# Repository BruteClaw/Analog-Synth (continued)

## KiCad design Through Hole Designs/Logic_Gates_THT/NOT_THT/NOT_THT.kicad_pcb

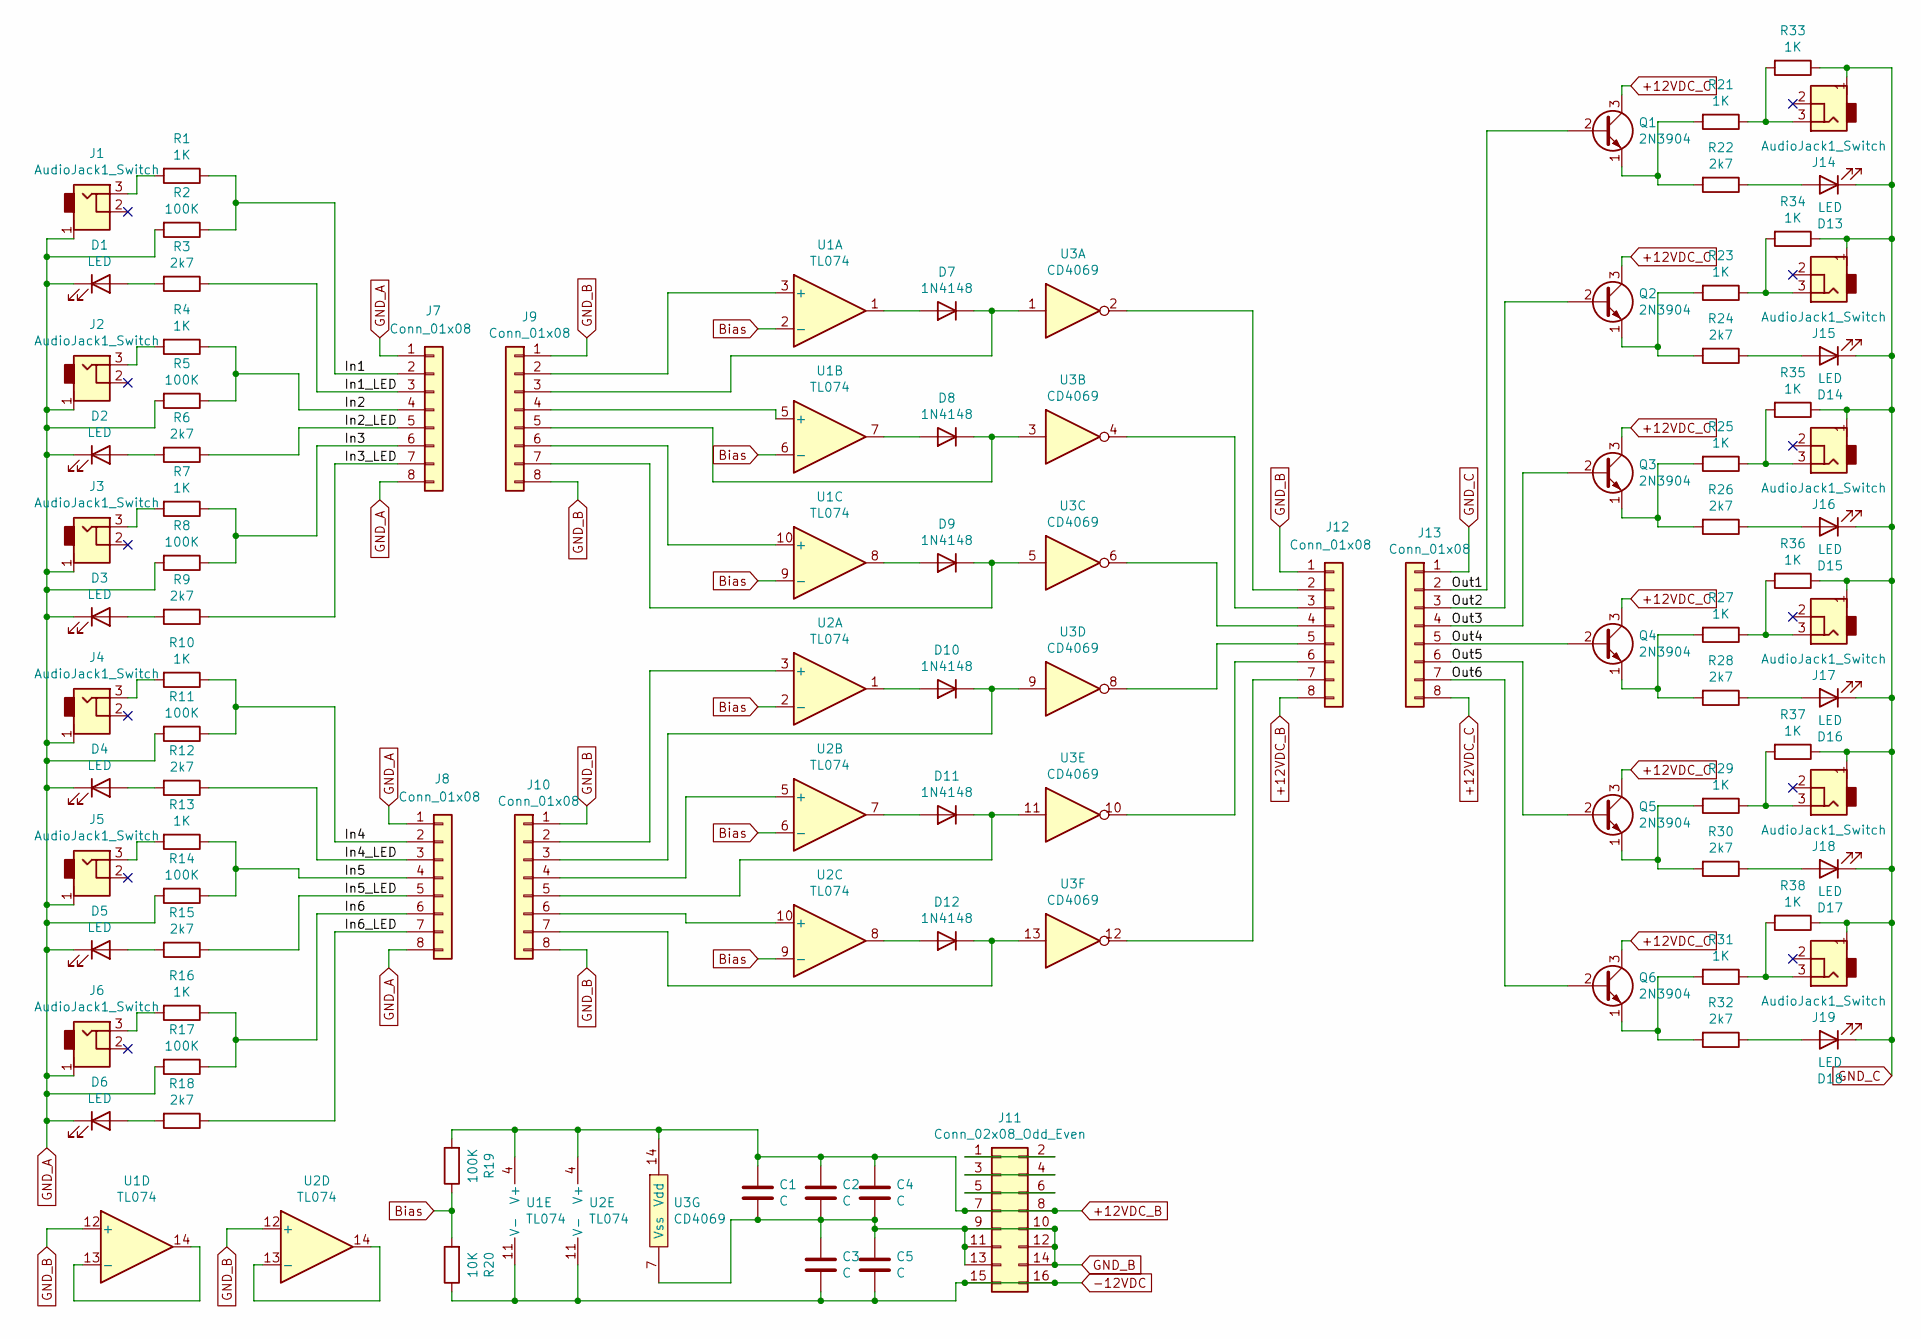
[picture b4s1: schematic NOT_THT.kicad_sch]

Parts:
C1, C2, C3, C4, C5: C; C_Disc_D5.0mm_W2.5mm_P2.50mm
D1, D2, D3, D4, D5, D6, D13, D14, D15, D16, D17, D18: LED; LED_Rectangular_W3.9mm_H1.9mm
D7, D8, D9, D10, D11, D12: 1N4148; D_DO-35_SOD27_P7.62mm_Horizontal
J1, J2, J3, J4, J5, J6, J14, J15, J16, J17, J18, J19: AudioJack1_Switch; Mono_Jack_3.5mm_Switch_Switchcraft_35RAPC2AH3
J7, J8, J9, J10, J12, J13: Conn_01x08; Pin_Header_Straight_1x08_Pitch2.54mm
J11: Conn_02x08_Odd_Even; Pin_Header_Straight_2x08_Pitch2.54mm
Q1, Q2, Q3, Q4, Q5, Q6: 2N3904; TO-92_Inline_Wide
R1, R4, R7, R10, R13, R16, R21, R23, R25, R27, R29, R31, R33, R34, R35, R36, R37, R38: 1K; R_Axial_DIN0207_L6.3mm_D2.5mm_P10.16mm_Horizontal
R2, R5, R8, R11, R14, R17, R19: 100K; R_Axial_DIN0207_L6.3mm_D2.5mm_P10.16mm_Horizontal
R3, R6, R9, R12, R15, R18, R22, R24, R26, R28, R30, R32: 2k7; R_Axial_DIN0207_L6.3mm_D2.5mm_P10.16mm_Horizontal
R20: 10K; R_Axial_DIN0207_L6.3mm_D2.5mm_P10.16mm_Horizontal
U1, U2: TL074; DIP-14_W7.62mm_Socket
U3: CD4069; DIP-14_W7.62mm_Socket

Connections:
+12VDC_B: C1.1, C2.1, C4.1, J11.7, J11.8, J12.8, R19.2, U1.4 (V+), U2.4 (V+), U3.14 (Vdd)
+12VDC_C: J13.8, Q1.3 (C), Q2.3 (C), Q3.3 (C), Q4.3 (C), Q5.3 (C), Q6.3 (C)
-12VDC: C3.2, C5.2, J11.15, J11.16, R20.1, U1.11 (V-), U2.11 (V-)
/In1: J7.2, R1.1, R2.1
/In1_LED: J7.3, R3.1
/In2: J7.4, R4.1, R5.1
/In2_LED: J7.5, R6.1
/In3: J7.6, R7.1, R8.1
/In3_LED: J7.7, R9.1
/In4: J8.2, R10.1, R11.1
/In4_LED: J8.3, R12.1
/In5: J8.4, R13.1, R14.1
/In5_LED: J8.5, R15.1
/In6: J8.6, R16.1, R17.1
/In6_LED: J8.7, R18.1
/Out1: J13.2, Q1.2 (B)
/Out2: J13.3, Q2.2 (B)
/Out3: J13.4, Q3.2 (B)
/Out4: J13.5, Q4.2 (B)
/Out5: J13.6, Q5.2 (B)
/Out6: J13.7, Q6.2 (B)
Bias: R19.1, R20.2, U1.2 (-), U1.6 (-), U1.9 (-), U2.2 (-), U2.6 (-), U2.9 (-)
GND_A: D1.1 (K), D2.1 (K), D3.1 (K), D4.1 (K), D5.1 (K), D6.1 (K), J1.1, J2.1, J3.1, J4.1, J5.1, J6.1, J7.1, J7.8, J8.1, J8.8, R2.2, R5.2, R8.2, R11.2, R14.2, R17.2
GND_B: C1.2, C2.2, C3.1, C4.2, C5.1, J9.1, J9.8, J10.1, J10.8, J11.9, J11.10, J11.11, J11.12, J11.13, J11.14, J12.1, U1.12 (+), U2.12 (+), U3.7 (Vss)
GND_C: D13.1 (K), D14.1 (K), D15.1 (K), D16.1 (K), D17.1 (K), D18.1 (K), J13.1, J14.1, J15.1, J16.1, J17.1, J18.1, J19.1, R33.1, R34.1, R35.1, R36.1, R37.1, R38.1
unnamed: D1.2 (A), R3.2
unnamed: D2.2 (A), R6.2
unnamed: D3.2 (A), R9.2
unnamed: D4.2 (A), R12.2
unnamed: D5.2 (A), R15.2
unnamed: D6.2 (A), R18.2
unnamed: D7.1 (K), J9.3, U3.1
unnamed: D7.2 (A), U1.1
unnamed: D8.1 (K), J9.5, U3.3
unnamed: D8.2 (A), U1.7
unnamed: D9.1 (K), J9.7, U3.5
unnamed: D9.2 (A), U1.8
unnamed: D10.1 (K), J10.3, U3.9
unnamed: D10.2 (A), U2.1
unnamed: D11.1 (K), J10.5, U3.11
unnamed: D11.2 (A), U2.7
unnamed: D12.1 (K), J10.7, U3.13
unnamed: D12.2 (A), U2.8
unnamed: D13.2 (A), R22.1
unnamed: D14.2 (A), R24.1
unnamed: D15.2 (A), R26.1
unnamed: D16.2 (A), R28.1
unnamed: D17.2 (A), R30.1
unnamed: D18.2 (A), R32.1
unnamed: J1.3, R1.2
unnamed: J2.3, R4.2
unnamed: J3.3, R7.2
unnamed: J4.3, R10.2
unnamed: J5.3, R13.2
unnamed: J6.3, R16.2
unnamed: J9.2, U1.3 (+)
unnamed: J9.4, U1.5 (+)
unnamed: J9.6, U1.10 (+)
unnamed: J10.2, U2.3 (+)
unnamed: J10.4, U2.5 (+)
unnamed: J10.6, U2.10 (+)
unnamed: J11.1, J11.2
unnamed: J11.3, J11.4
unnamed: J11.5, J11.6
unnamed: J12.2, U3.2
unnamed: J12.3, U3.4
unnamed: J12.4, U3.6
unnamed: J12.5, U3.8
unnamed: J12.6, U3.10
unnamed: J12.7, U3.12
unnamed: J14.3, R21.1, R33.2
unnamed: J15.3, R23.1, R34.2
unnamed: J16.3, R25.1, R35.2
unnamed: J17.3, R27.1, R36.2
unnamed: J18.3, R29.1, R37.2
unnamed: J19.3, R31.1, R38.2
unnamed: Q1.1 (E), R21.2, R22.2
unnamed: Q2.1 (E), R23.2, R24.2
unnamed: Q3.1 (E), R25.2, R26.2
unnamed: Q4.1 (E), R27.2, R28.2
unnamed: Q5.1 (E), R29.2, R30.2
unnamed: Q6.1 (E), R31.2, R32.2
unnamed: U1.13 (-), U1.14
unnamed: U2.13 (-), U2.14

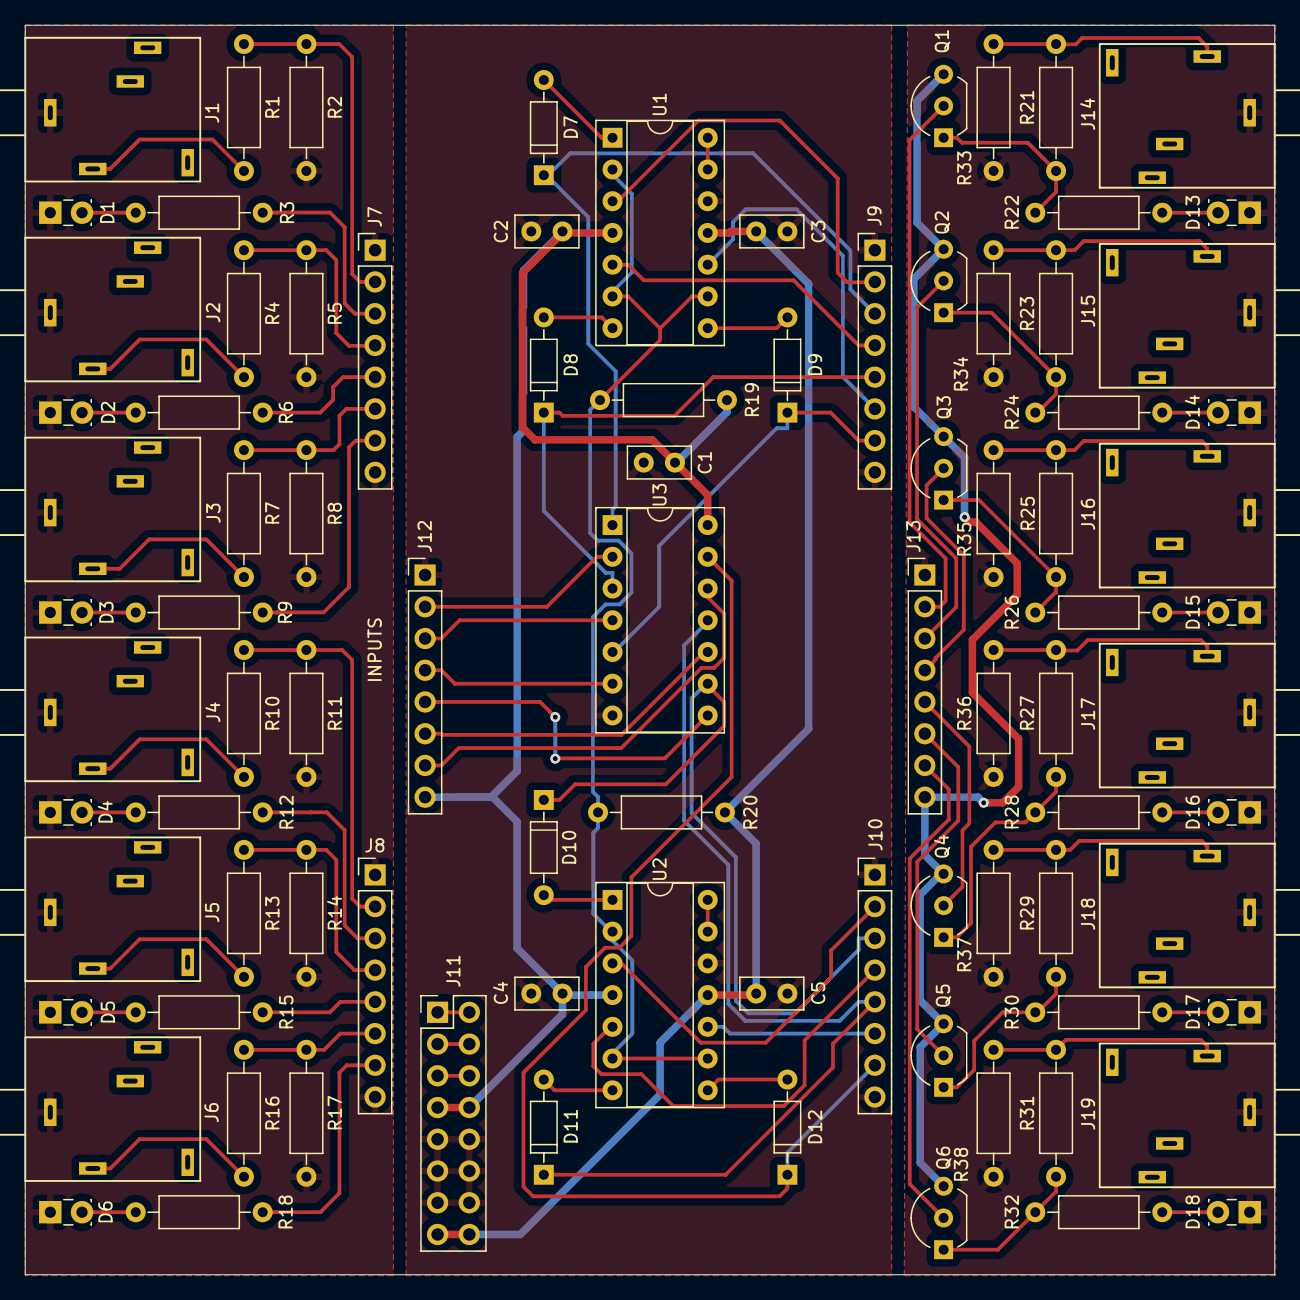
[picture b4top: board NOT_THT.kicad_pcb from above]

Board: 2 copper layers, 100.0 x 100.0 mm, 89 parts (0 on the bottom side), 84 nets.

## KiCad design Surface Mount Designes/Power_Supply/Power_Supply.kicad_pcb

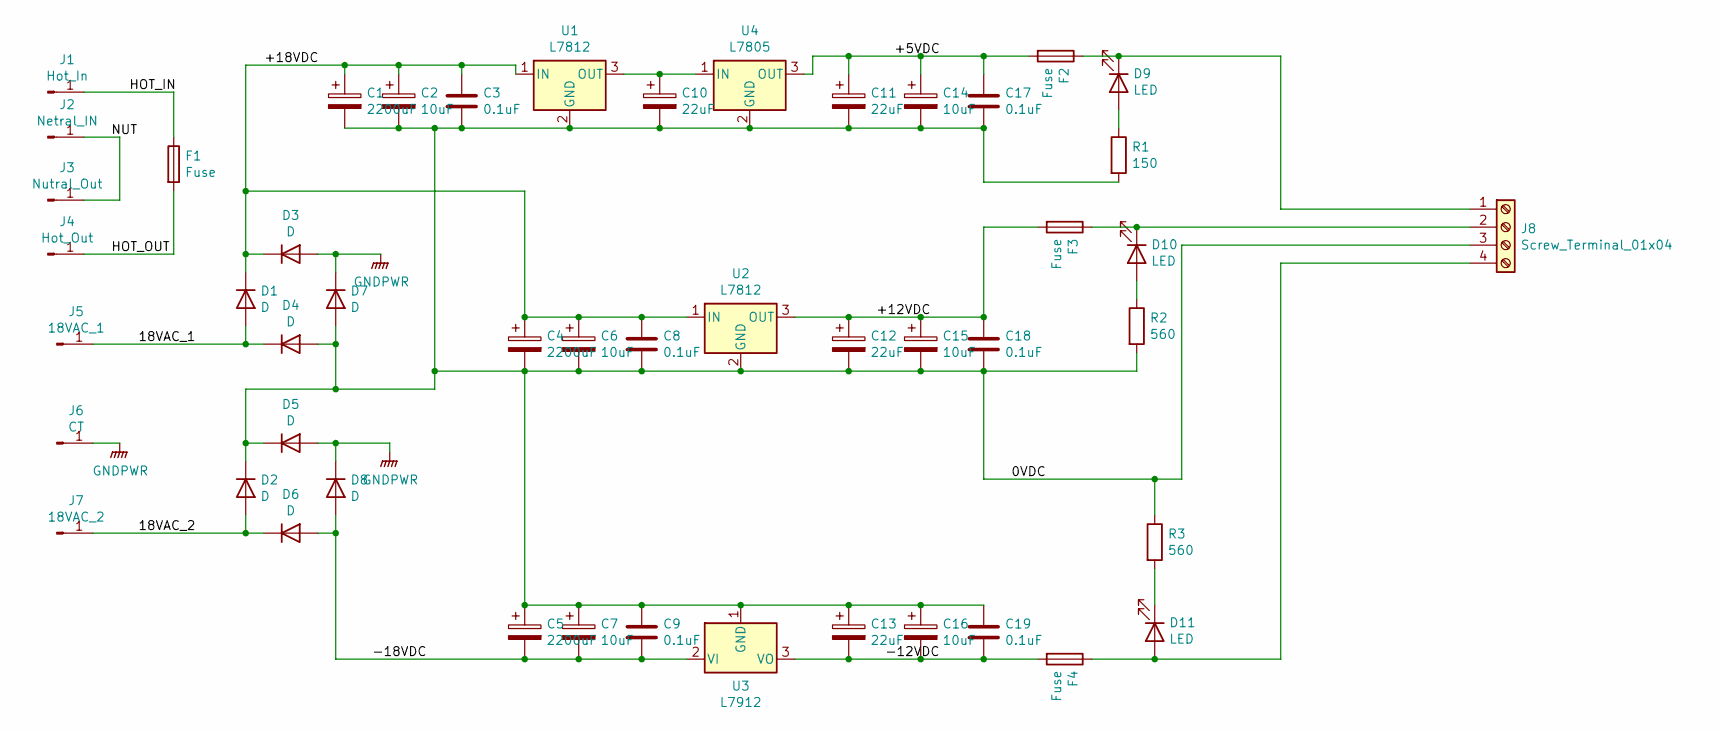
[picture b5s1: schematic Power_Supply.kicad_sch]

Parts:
C1, C4, C5: 2200uF; CP_Elec_18 x 21.5
C2, C6, C7, C14, C15, C16: 10uF; CP_Elec_5x5.3
C3, C8, C9, C17, C18, C19: 0.1uF; C_1206_HandSoldering
C10, C11, C12, C13: 22uF; CP_Elec_6.3x5.7
D1, D2, D3, D4, D5, D6, D7, D8: D; D_SMB
D9, D10, D11: LED; LED_1206_HandSoldering
F1, F2, F3, F4: Fuse; Fuseholder5x20_horiz_open_inline_Type-I
J1: Hot_In; TAB_Conn
J2: Netral_IN; TAB_Conn
J3: Nutral_Out; TAB_Conn
J4: Hot_Out; TAB_Conn
J5: 18VAC_1; TAB_Conn
J6: CT; TAB_Conn
J7: 18VAC_2; TAB_Conn
J8: Screw_Terminal_01x04; TerminalBlock_bornier-4_P5.08mm
R1: 150; R_1210_HandSoldering
R2, R3: 560; R_1210_HandSoldering
U1, U2: L7812; TO-252-2
U3: L7912; TO-263-2
U4: L7805; TO-252-2

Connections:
/0VDC: C1.2, C2.2, C3.2, C4.2, C5.1, C6.2, C7.1, C8.2, C9.1, C10.2, C11.2, C12.2, C13.1, C14.2, C15.2, C16.1, C17.2, C18.2, C19.1, D2.1 (K), D4.2 (A), D5.1 (K), D7.2 (A), J8.3, R1.2, R2.2, R3.1, U1.2 (GND), U2.2 (GND), U3.1 (GND), U4.2 (GND)
/18VAC_1: D1.2 (A), D4.1 (K), J5.1
/18VAC_2: D2.2 (A), D6.1 (K), J7.1
/+5VDC: C11.1, C14.1, C17.1, F2.2, U4.3 (OUT)
/+12VDC: C12.1, C15.1, C18.1, F3.2, U2.3 (OUT)
/+18VDC: C1.1, C2.1, C3.1, C4.1, C6.1, C8.1, D1.1 (K), D3.1 (K), U1.1 (IN), U2.1 (IN)
/-12VDC: C13.2, C16.2, C19.2, F4.2, U3.3 (VO)
/-18VDC: C5.2, C7.2, C9.2, D6.2 (A), D8.2 (A), U3.2 (VI)
/HOT_IN: F1.1, J1.1
/HOT_OUT: F1.2, J4.1
/NUT: J2.1, J3.1
GNDPWR: D3.2 (A), D5.2 (A), D7.1 (K), D8.1 (K), J6.1
unnamed: C10.1, U1.3 (OUT), U4.1 (IN)
unnamed: D9.1 (K), F2.1, J8.1
unnamed: D9.2 (A), R1.1
unnamed: D10.1 (K), F3.1, J8.2
unnamed: D10.2 (A), R2.1
unnamed: D11.1 (K), R3.2
unnamed: D11.2 (A), F4.1, J8.4

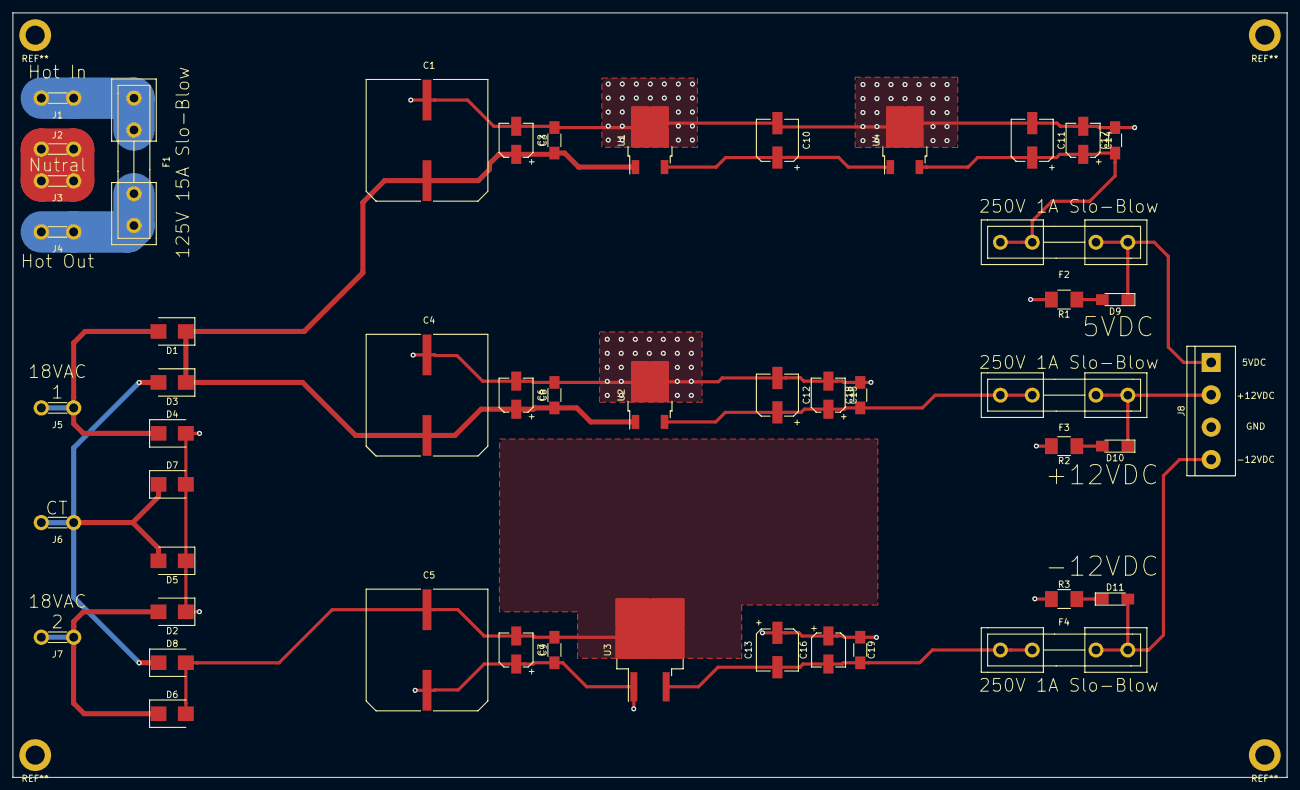
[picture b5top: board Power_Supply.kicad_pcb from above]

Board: 2 copper layers, 200.0 x 120.0 mm, 49 parts (0 on the bottom side), 19 nets.

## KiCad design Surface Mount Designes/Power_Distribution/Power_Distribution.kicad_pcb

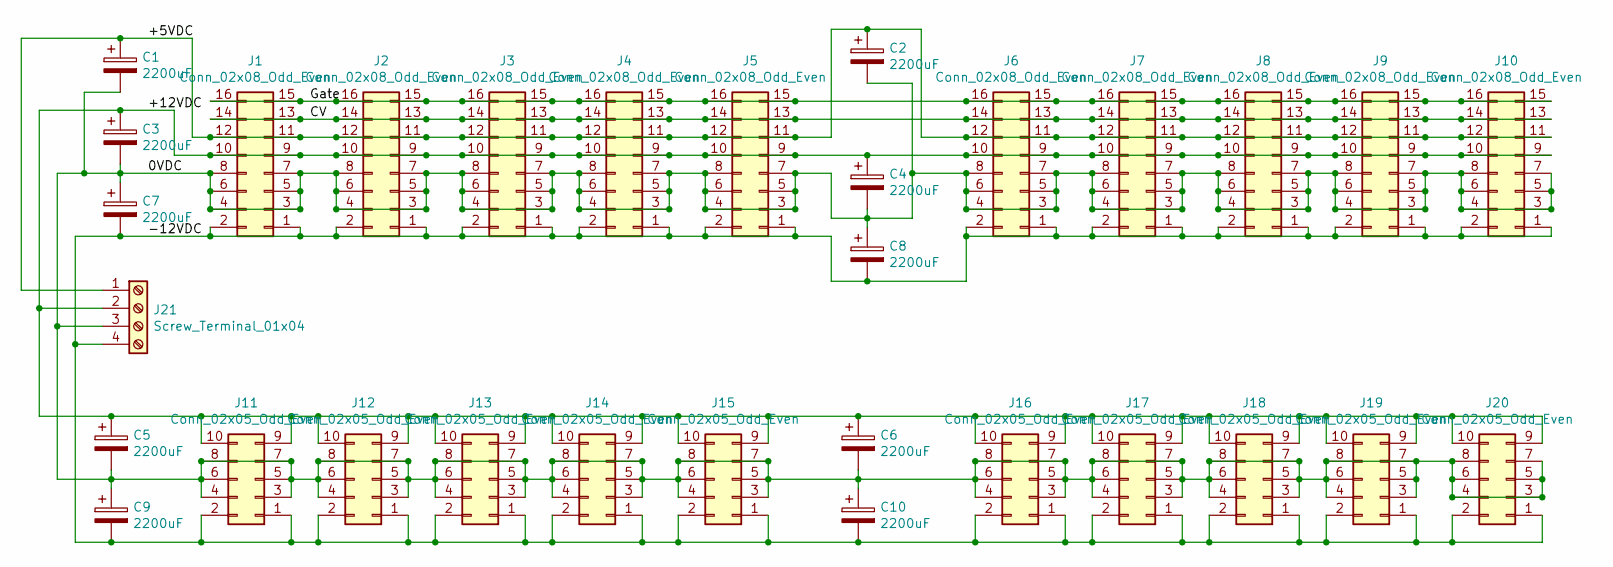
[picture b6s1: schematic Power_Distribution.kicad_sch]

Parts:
C1, C2, C3, C4, C5, C6, C7, C8, C9, C10: 2200uF; CP_Elec_18 x 21.5
J1, J2, J3, J4, J5, J6, J7, J8, J9, J10: Conn_02x08_Odd_Even; Socket_Strip_Straight_2x08_Pitch2.54mm
J11, J12, J13, J14, J15, J16, J17, J18, J19, J20: Conn_02x05_Odd_Even; Socket_Strip_Straight_2x05_Pitch2.54mm
J21: Screw_Terminal_01x04; TerminalBlock_bornier-4_P5.08mm

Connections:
/0VDC: C1.2, C2.2, C3.2, C4.2, C5.2, C6.2, C7.1, C8.1, C9.1, C10.1, J1.3, J1.4, J1.5, J1.6, J1.7, J1.8, J2.3, J2.4, J2.5, J2.6, J2.7, J2.8, J3.3, J3.4, J3.5, J3.6, J3.7, J3.8, J4.3, J4.4, J4.5, J4.6, J4.7, J4.8, J5.3, J5.4, J5.5, J5.6, J5.7, J5.8, J6.3, J6.4, J6.5, J6.6, J6.7, J6.8, J7.3, J7.4, J7.5, J7.6, J7.7, J7.8, J8.3, J8.4, J8.5, J8.6, J8.7, J8.8, J9.3, J9.4, J9.5, J9.6, J9.7, J9.8, J10.3, J10.4, J10.5, J10.6, J10.7, J10.8, J11.3, J11.4, J11.5, J11.6, J11.7, J11.8, J12.3, J12.4, J12.5, J12.6, J12.7, J12.8, J13.3, J13.4, J13.5, J13.6, J13.7, J13.8, J14.3, J14.4, J14.5, J14.6, J14.7, J14.8, J15.3, J15.4, J15.5, J15.6, J15.7, J15.8, J16.3, J16.4, J16.5, J16.6, J16.7, J16.8, J17.3, J17.4, J17.5, J17.6, J17.7, J17.8, J18.3, J18.4, J18.5, J18.6, J18.7, J18.8, J19.3, J19.4, J19.5, J19.6, J19.7, J19.8, J20.3, J20.4, J20.5, J20.6, J20.7, J20.8, J21.3
/+5VDC: C1.1, C2.1, J1.11, J1.12, J2.11, J2.12, J3.11, J3.12, J4.11, J4.12, J5.11, J5.12, J6.11, J6.12, J7.11, J7.12, J8.11, J8.12, J9.11, J9.12, J10.11, J10.12, J21.1
/+12VDC: C3.1, C4.1, C5.1, C6.1, J1.9, J1.10, J2.9, J2.10, J3.9, J3.10, J4.9, J4.10, J5.9, J5.10, J6.9, J6.10, J7.9, J7.10, J8.9, J8.10, J9.9, J9.10, J10.9, J10.10, J11.9, J11.10, J12.9, J12.10, J13.9, J13.10, J14.9, J14.10, J15.9, J15.10, J16.9, J16.10, J17.9, J17.10, J18.9, J18.10, J19.9, J19.10, J20.9, J20.10, J21.2
/-12VDC: C7.2, C8.2, C9.2, C10.2, J1.1, J1.2, J2.1, J2.2, J3.1, J3.2, J4.1, J4.2, J5.1, J5.2, J6.1, J6.2, J7.1, J7.2, J8.1, J8.2, J9.1, J9.2, J10.1, J10.2, J11.1, J11.2, J12.1, J12.2, J13.1, J13.2, J14.1, J14.2, J15.1, J15.2, J16.1, J16.2, J17.1, J17.2, J18.1, J18.2, J19.1, J19.2, J20.1, J20.2, J21.4
/CV: J1.13, J1.14, J2.13, J2.14, J3.13, J3.14, J4.13, J4.14, J5.13, J5.14, J6.13, J6.14, J7.13, J7.14, J8.13, J8.14, J9.13, J9.14, J10.13, J10.14
/Gate: J1.15, J1.16, J2.15, J2.16, J3.15, J3.16, J4.15, J4.16, J5.15, J5.16, J6.15, J6.16, J7.15, J7.16, J8.15, J8.16, J9.15, J9.16, J10.15, J10.16

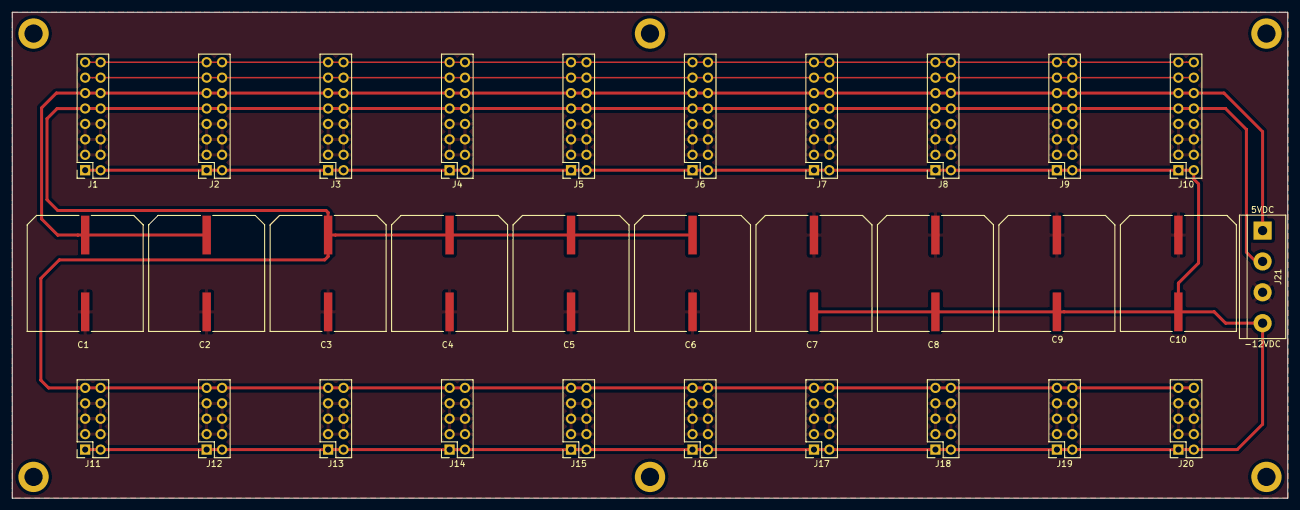
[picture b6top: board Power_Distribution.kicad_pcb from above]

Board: 2 copper layers, 210.0 x 80.0 mm, 31 parts (0 on the bottom side), 6 nets.

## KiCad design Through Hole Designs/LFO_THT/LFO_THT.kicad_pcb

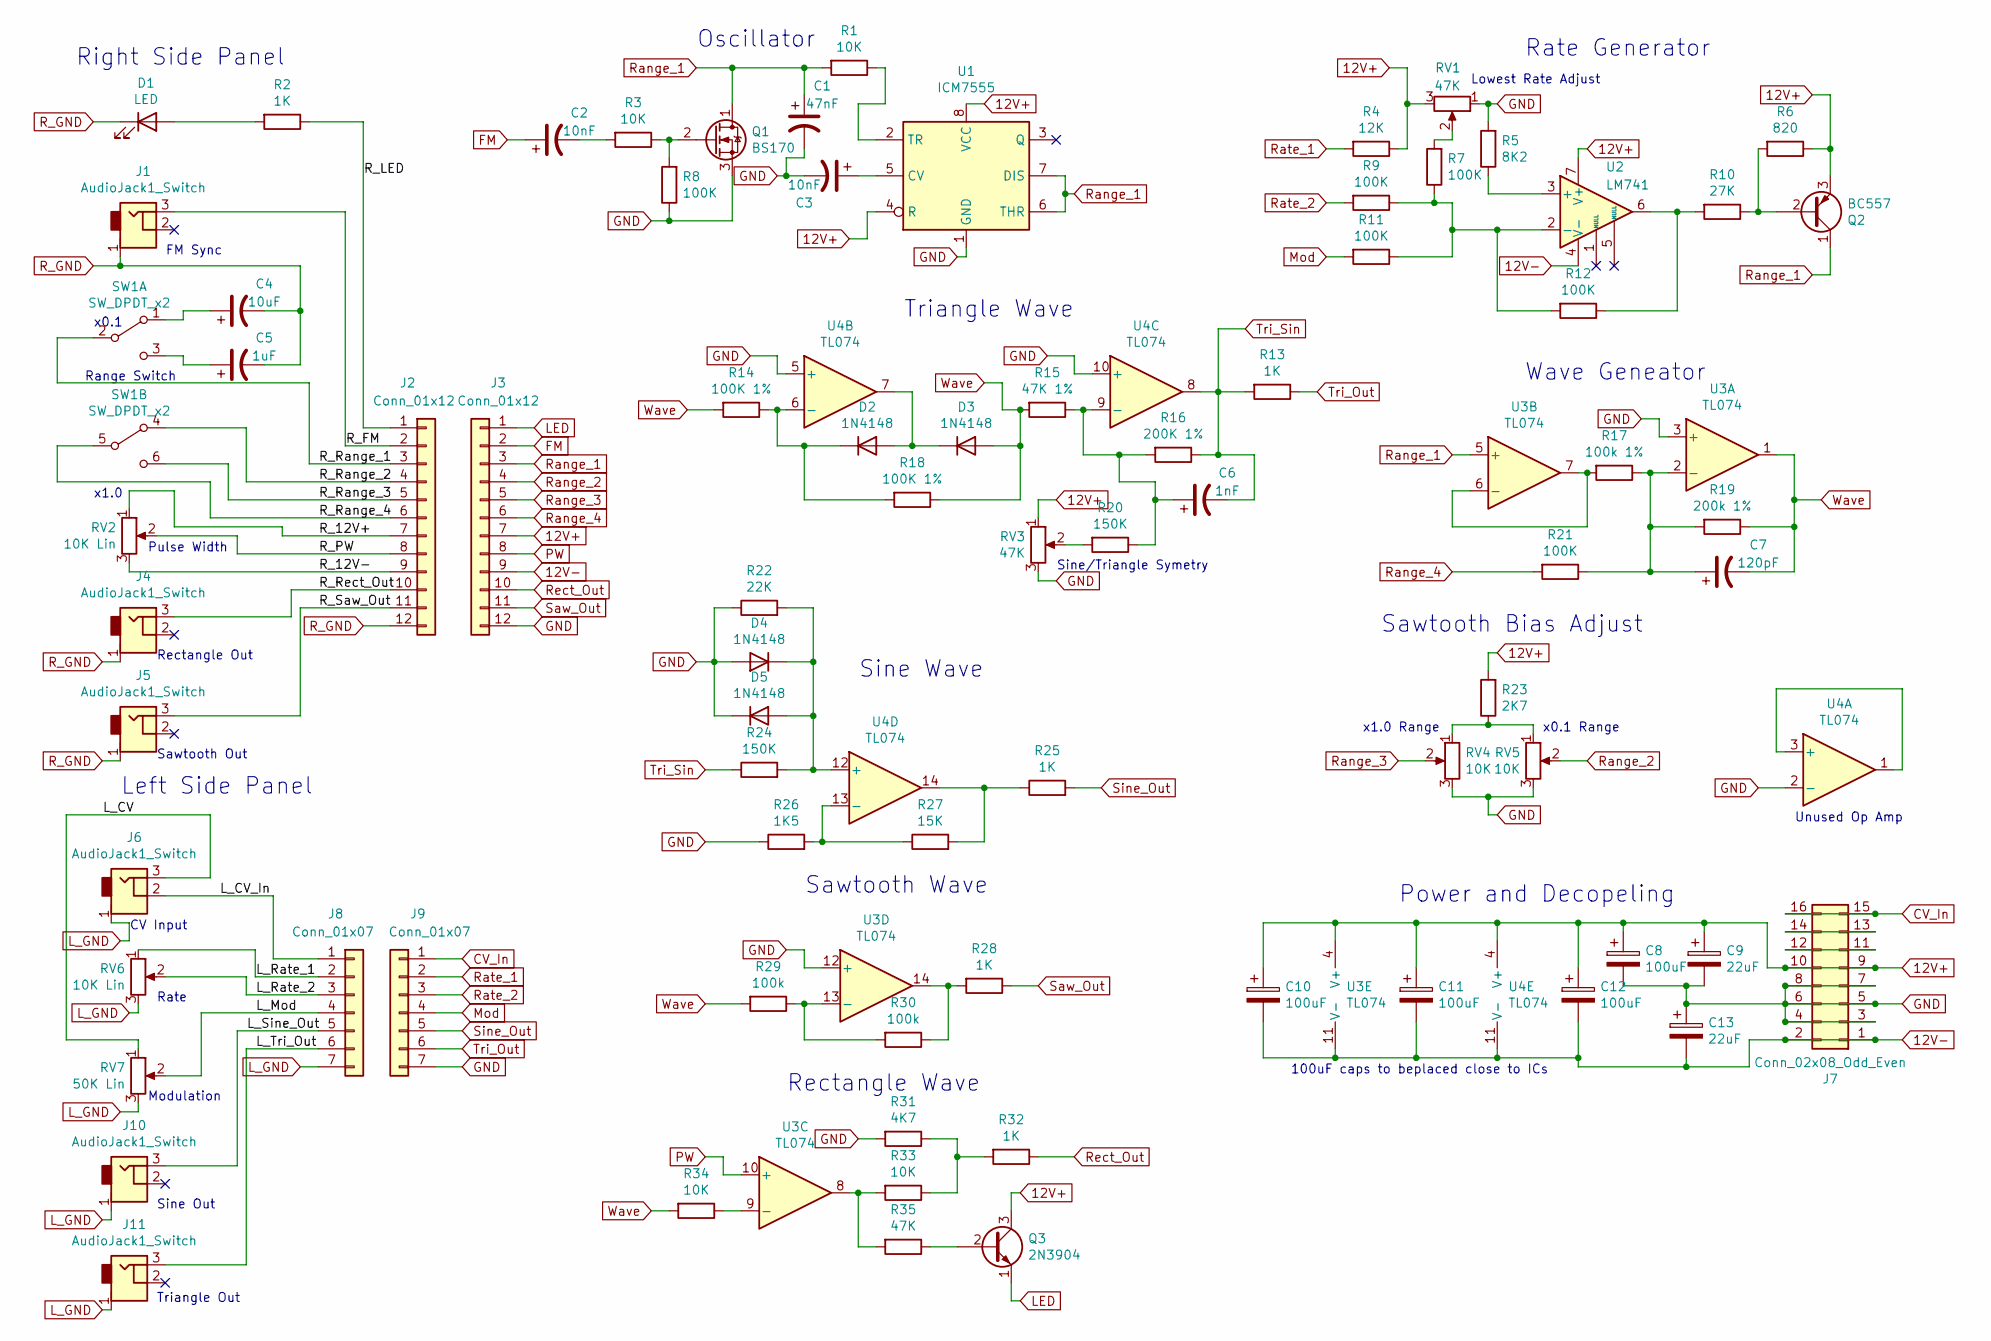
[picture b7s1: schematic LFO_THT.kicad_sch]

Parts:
C1: 47nF; C_Disc_D5.0mm_W2.5mm_P5.00mm
C2, C3: 10nF; C_Disc_D5.0mm_W2.5mm_P5.00mm
C4: 10uF; C_Disc_D5.0mm_W2.5mm_P5.00mm
C5: 1uF; C_Disc_D5.0mm_W2.5mm_P5.00mm
C6: 1nF; C_Disc_D5.0mm_W2.5mm_P5.00mm
C7: 120pF; C_Disc_D5.0mm_W2.5mm_P5.00mm
C8, C10, C11, C12: 100uF; CP_Radial_D6.3mm_P2.50mm
C9, C13: 22uF; CP_Radial_D5.0mm_P2.00mm
D1: LED; LED_Rectangular_W3.9mm_H1.9mm
D2, D3, D4, D5: 1N4148; D_DO-35_SOD27_P7.62mm_Horizontal
J1, J4, J5, J6, J10, J11: AudioJack1_Switch; Mono_Jack_3.5mm_Switch_Switchcraft_35RAPC2AH3
J2, J3: Conn_01x12; Pin_Header_Straight_1x12_Pitch2.54mm
J7: Conn_02x08_Odd_Even; Pin_Header_Straight_2x08_Pitch2.54mm
J8, J9: Conn_01x07; Pin_Header_Straight_1x07_Pitch2.54mm
Q1: BS170; TO-92_Inline_Wide
Q2: BC557; TO-92_Inline_Wide
Q3: 2N3904; TO-92_Inline_Wide
R1, R3, R33, R34: 10K; R_Axial_DIN0207_L6.3mm_D2.5mm_P10.16mm_Horizontal
R2, R13, R25, R28, R32: 1K; R_Axial_DIN0207_L6.3mm_D2.5mm_P10.16mm_Horizontal
R4: 12K; R_Axial_DIN0207_L6.3mm_D2.5mm_P10.16mm_Horizontal
R5: 8K2; R_Axial_DIN0207_L6.3mm_D2.5mm_P10.16mm_Horizontal
R6: 820; R_Axial_DIN0207_L6.3mm_D2.5mm_P10.16mm_Horizontal
R7, R8, R9, R11, R12, R21: 100K; R_Axial_DIN0207_L6.3mm_D2.5mm_P10.16mm_Horizontal
R10: 27K; R_Axial_DIN0207_L6.3mm_D2.5mm_P10.16mm_Horizontal
R14, R18: 100K 1%; R_Axial_DIN0207_L6.3mm_D2.5mm_P10.16mm_Horizontal
R15: 47K 1%; R_Axial_DIN0207_L6.3mm_D2.5mm_P10.16mm_Horizontal
R16: 200K 1%; R_Axial_DIN0207_L6.3mm_D2.5mm_P10.16mm_Horizontal
R17: 100k 1%; R_Axial_DIN0207_L6.3mm_D2.5mm_P10.16mm_Horizontal
R19: 200k 1%; R_Axial_DIN0207_L6.3mm_D2.5mm_P10.16mm_Horizontal
R20, R24: 150K; R_Axial_DIN0207_L6.3mm_D2.5mm_P10.16mm_Horizontal
R22: 22K; R_Axial_DIN0207_L6.3mm_D2.5mm_P10.16mm_Horizontal
R23: 2K7; R_Axial_DIN0207_L6.3mm_D2.5mm_P10.16mm_Horizontal
R26: 1K5; R_Axial_DIN0207_L6.3mm_D2.5mm_P10.16mm_Horizontal
R27: 15K; R_Axial_DIN0207_L6.3mm_D2.5mm_P10.16mm_Horizontal
R29, R30: 100k; R_Axial_DIN0207_L6.3mm_D2.5mm_P10.16mm_Horizontal
R31: 4K7; R_Axial_DIN0207_L6.3mm_D2.5mm_P10.16mm_Horizontal
R35: 47K; R_Axial_DIN0207_L6.3mm_D2.5mm_P10.16mm_Horizontal
RV1, RV3: 47K; Potentiometer_Trimmer_Piher_PT-10v10_Horizontal_Px10.0mm_Py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
RV2, RV6: 10K Lin; Potentiometer_Bourns_PTV09A-2_Vertical
RV4, RV5: 10K; TT_64WR10KLF
RV7: 50K Lin; Potentiometer_Bourns_PTV09A-2_Vertical
SW1: SW_DPDT_x2; 200AWMDP1T2A1M6QE
U1: ICM7555; DIP-8_W7.62mm_Socket
U2: LM741; DIP-8_W7.62mm_Socket
U3, U4: TL074; DIP-14_W7.62mm_Socket

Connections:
12V+: C8.1, C9.1, C10.1, C11.1, C12.1, J3.7, J7.9, J7.10, Q2.3 (E), Q3.3 (C), R4.1, R6.1, R23.2, RV1.3, RV3.1, U1.4 (R), U1.8 (VCC), U2.7 (V+), U3.4 (V+), U4.4 (V+)
12V-: C10.2, C11.2, C12.2, C13.2, J3.9, J7.1, J7.2, U2.4 (V-), U3.11 (V-), U4.11 (V-)
/L_CV: J6.3, RV7.1
/L_CV_In: J6.2, J8.1
/L_Mod: J8.4, RV7.2
/L_Rate_1: J8.2, RV6.1
/L_Rate_2: J8.3, RV6.2
/L_Sine_Out: J8.5, J10.3
/L_Tri_Out: J8.6, J11.3
/R_12V+: J2.7, RV2.1
/R_12V-: J2.9, RV2.3
/R_FM: J1.3, J2.2
/R_LED: J2.1, R2.1
/R_PW: J2.8, RV2.2
/R_Range_1: J2.3, SW1.2 (B)
/R_Range_2: J2.4, SW1.4 (A)
/R_Range_3: J2.5, SW1.6 (C)
/R_Range_4: J2.6, SW1.5 (B)
/R_Rect_Out: J2.10, J4.3
/R_Saw_Out: J2.11, J5.3
CV_In: J7.15, J7.16, J9.1
FM: C2.1, J3.2
GND: C1.2, C3.2, C8.2, C9.2, C13.1, D4.2 (A), D5.1 (K), J3.12, J7.3, J7.4, J7.5, J7.6, J7.7, J7.8, J9.7, Q1.3 (S), R5.2, R8.1, R22.1, R26.1, R31.2, RV1.1, RV3.3, RV4.3, RV5.3, U1.1 (GND), U3.3 (+), U3.12 (+), U4.2 (-), U4.5 (+), U4.10 (+)
LED: J3.1, Q3.1 (E)
L_GND: J6.1, J8.7, J10.1, J11.1, RV6.3, RV7.3
Mod: J9.4, R11.2
unnamed: C2.2, R3.2
unnamed: C3.1, U1.5 (CV)
unnamed: C4.1, SW1.1 (A)
unnamed: C5.1, SW1.3 (C)
unnamed: C6.1, R15.1, R16.2, R20.1, U4.9 (-)
unnamed: C7.1, R17.1, R19.2, R21.1, U3.2 (-)
unnamed: D1.2 (A), R2.2
unnamed: D2.1 (K), R14.1, R18.2, U4.6 (-)
unnamed: D2.2 (A), D3.1 (K), U4.7
unnamed: D4.1 (K), D5.2 (A), R22.2, R24.2, U4.12 (+)
unnamed: J7.11, J7.12
unnamed: J7.13, J7.14
unnamed: Q1.2 (G), R3.1, R8.2
unnamed: Q2.2 (B), R6.2, R10.1
unnamed: Q3.2 (B), R35.1
unnamed: R1.1, U1.2 (TR)
unnamed: R5.1, U2.3 (+)
unnamed: R7.2, RV1.2
unnamed: R10.2, R12.1, U2.6
unnamed: R7.1, R9.1, R11.1, R12.2, U2.2 (-)
unnamed: R17.2, U3.6 (-), U3.7
unnamed: R20.2, RV3.2
unnamed: R23.1, RV4.1, RV5.1
unnamed: R25.1, R27.2, U4.14
unnamed: R26.2, R27.1, U4.13 (-)
unnamed: R28.2, R30.1, U3.14
unnamed: R29.1, R30.2, U3.13 (-)
unnamed: R31.1, R32.2, R33.1
unnamed: R33.2, R35.2, U3.8
unnamed: R34.1, U3.9 (-)
unnamed: U4.1, U4.3 (+)
PW: J3.8, U3.10 (+)
R_GND: C4.2, C5.2, D1.1 (K), J1.1, J2.12, J4.1, J5.1
Range_1: C1.1, J3.3, Q1.1 (D), Q2.1 (C), R1.2, U1.6 (THR), U1.7 (DIS), U3.5 (+)
Range_2: J3.4, RV5.2
Range_3: J3.5, RV4.2
Range_4: J3.6, R21.2
Rate_1: J9.2, R4.2
Rate_2: J9.3, R9.2
Rect_Out: J3.10, R32.1
Saw_Out: J3.11, R28.1
Sine_Out: J9.5, R25.2
Tri_Out: J9.6, R13.1
Tri_Sin: C6.2, R13.2, R16.1, R24.1, U4.8
Wave: C7.2, D3.2 (A), R14.2, R15.2, R18.1, R19.1, R29.2, R34.2, U3.1

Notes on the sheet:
x0.1 Range
Rate Generator
Wave Geneator
Modulation
Sawtooth Wave
Sine Wave
Triangle Out
FM Sync
Sine/Triangle Symetry
Sine Out
Left Side Panel
Sawtooth Bias Adjust
Rate
Lowest Rate Adjust
Unused Op Amp
100uF caps to beplaced close to ICs
CV Input
x1.0 Range
Pulse Width
Right Side Panel
Oscillator
Sawtooth Out
Rectangle Out
Range Switch
Rectangle Wave
Power and Decopeling
Triangle Wave
x0.1
x1.0

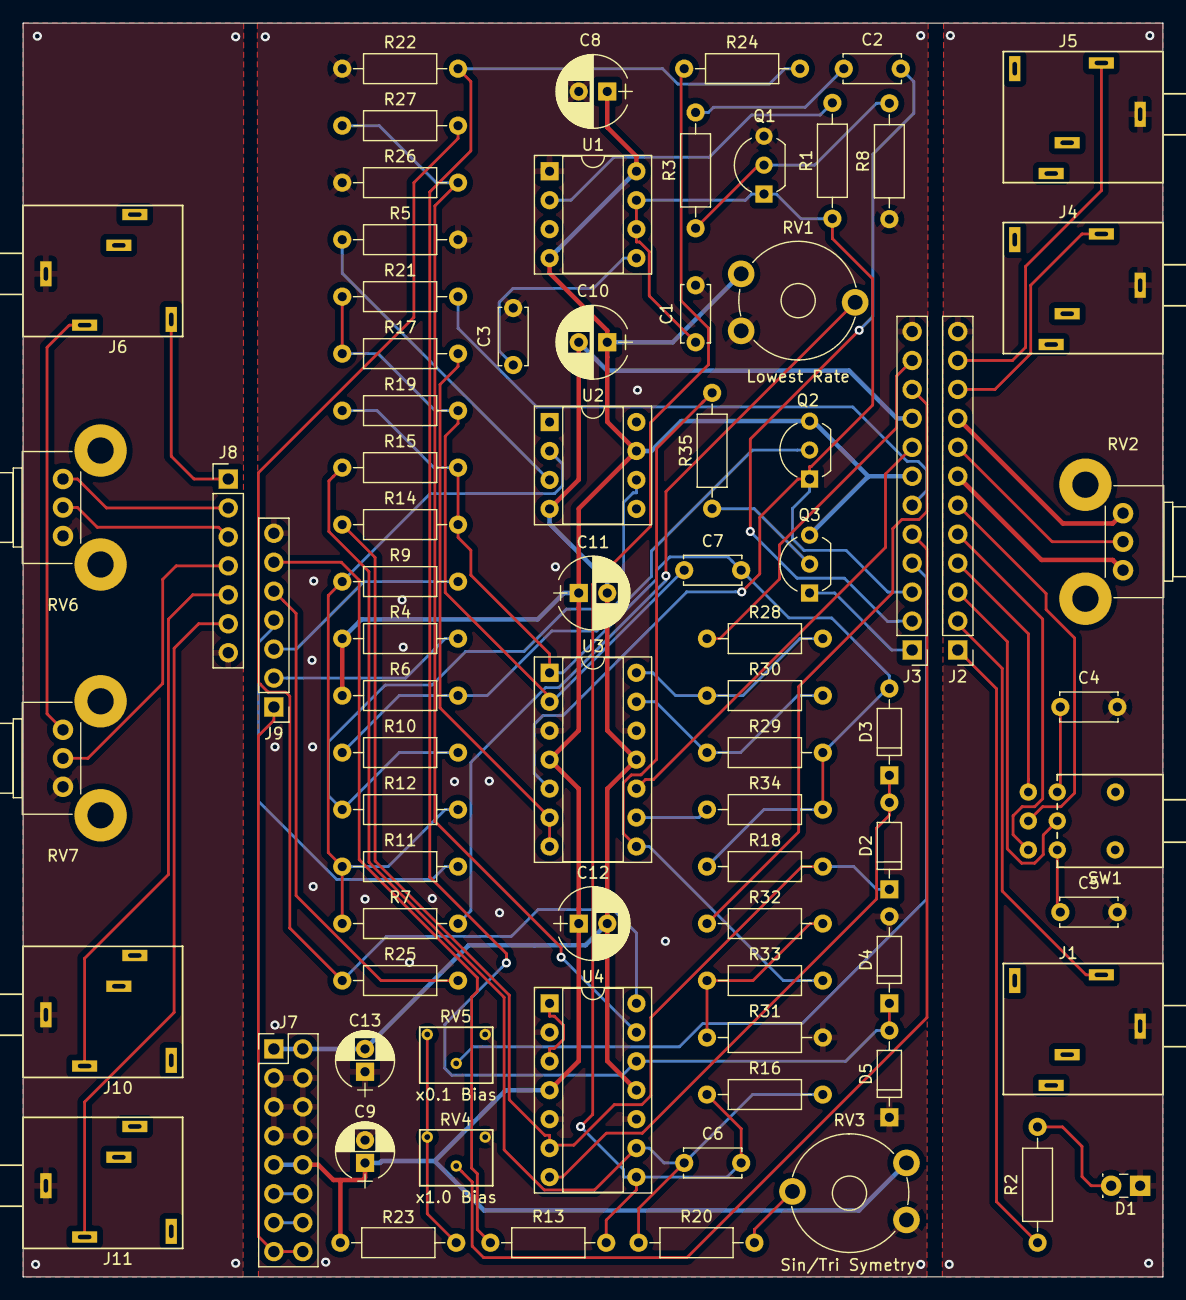
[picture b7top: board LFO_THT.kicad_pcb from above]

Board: 2 copper layers, 100.0 x 110.0 mm, 79 parts (0 on the bottom side), 71 nets.

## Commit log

2020-11-25 Initial Commits
    Initial commit to GitHub andcleaning out files that were not needed
2020-11-26 ADSR Envelope
    Updated the Schematic for the ADSR Envilope and started on the PCB layout
2020-11-26 ADSR Envelope
    Finished the PCB design on the ADSR Envelope
2020-12-04 Add files via upload
    added PDF of schematic for Notch Filter
2020-12-06 LFO And Schematics
    Finished ADSR SMD board design. Created PDFs of all the schemaitcs for finsihed designs. Created LFO THT schematic, board design and BOM.
2020-12-06 Update Notes.txt
    Adding to Notes for a Midi to CV design I found on another GitHub
2020-12-07 LFO SMD
    Created the SMD version the the LFO and corrisponding BOM.
2020-12-09 Re-Organize
    Reorganized how designs are sorted in the repository. Also exported all custom footprints into the project folder for easy modificcation by other people later
2020-12-10 KiCAD Update Test
    Updated KiCad and tested loading a file
2020-12-10 unmotivated
2021-01-16 Comb Filter
    Started design on Comb Filter
2021-01-17 Comb
    Finished The Schematic for the Comb Filter and started on the Surface Mount PCB design
2021-01-29 1-29-2021 Comb
    Started Layout of Comb Filter
2022-04-10 Update Summary
    Updated the Overall Desdign File
2022-04-10 KiCAD 6.0 Update
    Updated all the project files to Version 6.0 of KiCAD. No change to Gerbers or Schematics.
2022-04-10 Comb Placements
    started placing components on Comb Filter
2022-11-20 KiCAD Update
    Verifying files would open in updated version of KiCAD
2025-02-23 Reinstalling GIT Desktop
2025-02-23 KiCad 9.0 Update
    Installed KiCad 9.0 and updated all the files to latest version before continuing work on the designs.
